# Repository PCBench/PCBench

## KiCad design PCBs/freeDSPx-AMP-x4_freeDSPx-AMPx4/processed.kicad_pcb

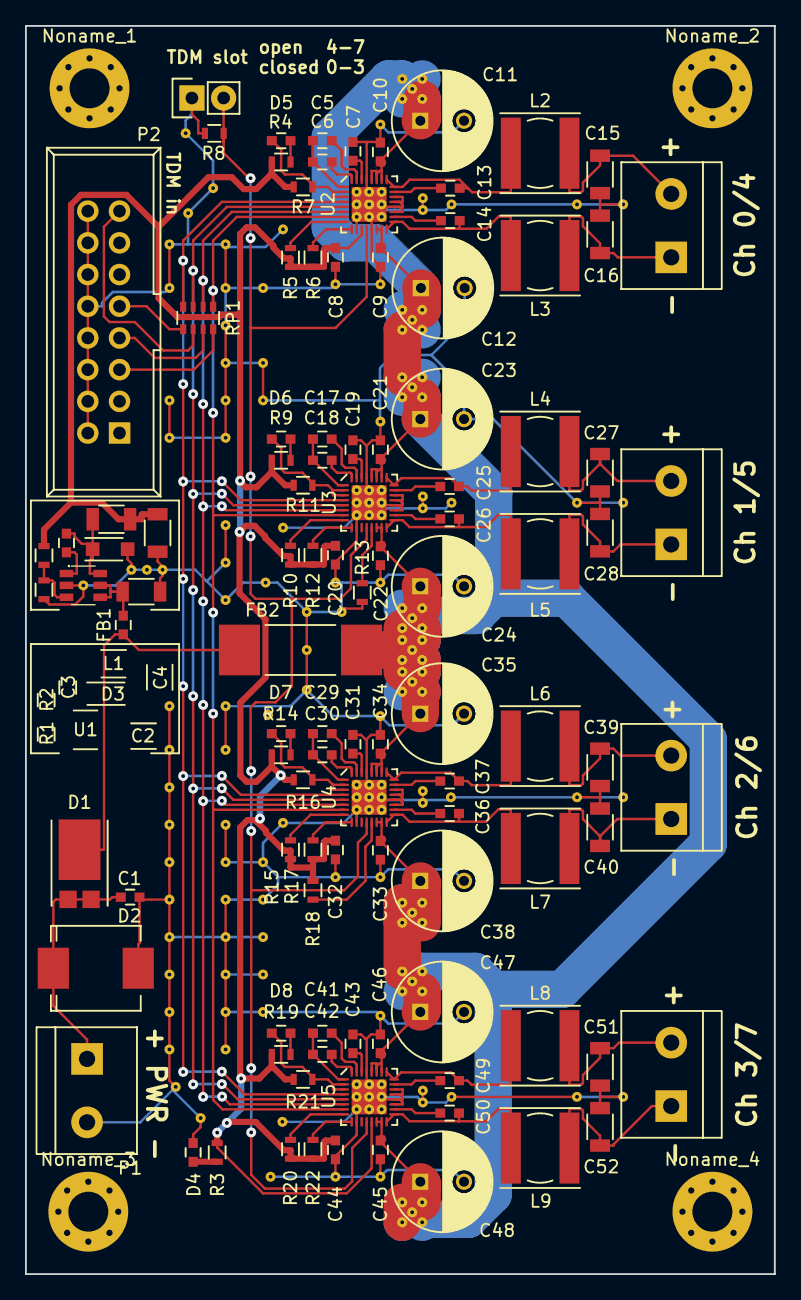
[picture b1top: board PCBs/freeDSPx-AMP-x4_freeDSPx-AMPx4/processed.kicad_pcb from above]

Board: 2 copper layers, 60.0 x 100.0 mm, 283 parts (0 on the bottom side), 77 nets.

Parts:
C1, C3, C9, C10, C21, C22, C33, C34, C45, C46: 100n/50V; C_0603
C2: 10u/35V; C_1206
C4: 22u/10V; C_1206
C5, C6, C7, C8, C17, C18, C19, C20, C29, C30, C31, C32, C41, C42, C43, C44: 1u/16V; C_0603
C11, C12, C23, C24, C35, C36, C47, C48: 100u/35V; C_Radial_D8_L11.5_P3.5
C13, C14, C25, C26, C37, C38, C49, C50: 220n/25V; C_0603
C15, C16, C27, C28, C39, C40, C51, C52: 680n/50V; C_1206
D1: SBR10E45P5; PowerDI5
D2: 5.0SMDJ28CA; SMC
D3: PMEG6010ER; SOD-123W
D4, D5, D6, D7, D8: LED; C_0603
FB1: 470; C_0603
FB2: 115; C_3312
JP1: JUMPER; Pin_Header_Straight_1x02
L1: 47u; L_1207
L2, L3, L4, L5, L6, L7, L8, L9: 15u; Choke_SMD_6.0x6.0
Noname_1, Noname_2, Noname_3, Noname_4: MountingHole_3.2mm_M3_Pad_Via
None_1, None_2, None_3, None_4, None_5, None_6, None_7, None_8, None_9, None_10, None_11, None_12, None_13, None_14, None_15, None_16, None_17, None_18, None_19, None_20, None_21, None_22, None_23, None_24, None_25, None_26, None_27, None_28, None_29, None_30, None_31, None_32, None_33, None_34, None_35, None_36, None_37, None_38, None_39, None_40, None_41, None_42, None_43, None_44, None_45, None_46, None_47, None_48, None_49, None_50, None_51, None_52, None_53, None_54, None_55, None_56, None_57, None_58, None_59, None_60, None_61, None_62, None_63, None_64, None_65, None_66, None_67, None_68, None_69, None_70, None_71, None_72, None_73, None_74, None_75, None_76, None_77, None_78, None_79, None_80, None_81, None_82, None_83, None_84, None_85, None_86, None_87, None_88, None_89, None_90, None_91, None_92, None_93, None_94, None_95, None_96, None_97, None_98, None_99, None_100, None_101, None_102, None_103, None_104, None_105, None_106, None_107, None_108, None_109, None_110, None_111, None_112, None_113, None_114, None_115, None_116, None_117, None_118, None_119, None_120, None_121, None_122, None_123, None_124, None_125, None_126, None_127, None_128, None_129, None_130, None_131, None_132, None_133, None_134, None_135, None_136, None_137, None_138, None_139, None_140, None_141, None_142, None_143, None_144, None_145, None_146, None_147, None_148, None_149, None_150, None_151, None_152, None_153, None_154, None_155, None_156, None_157, None_158, None_159, None_160, None_161, None_162, None_163, None_164, None_165, None_166, None_167, None_168, None_169, None_170, None_171, None_172, None_173: Via_0.3mm_0.8mm
P1, P3, P4, P5, P6: CONN_01X02; RIACON101-2
P2: STDCONN; IDC_Header_Straight_16pins
R1: 1k2; R_0603
R2: 3k4; R_0603
R3, R4, R9, R14, R19: 620; R_0603
R5, R6, R10, R12, R15, R17, R20, R22: 2k4; R_0603
R7, R11, R16, R21: 100k; R_0603
R8, R13, R18: 22k; R_0603
RP1: 33; R_Array_Convex_4x0603
U1: LM2841X; SOT23-6_1.7x3.0mm_Pitch0.95mm
U2, U3, U4, U5: TAS5720M; VQFN-32_4x4mm_Pitch0.4mm

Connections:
+3V3: C4.2, C8.2, C20.2, C32.2, C44.2, L1.2, R2.1, R3.2, R4.1, R5.1, R6.1, R7.1, R9.1, R10.1, R11.1, R12.1, R14.1, R15.1, R16.1, R17.1, R18.2, R19.1, R20.1, R21.1, R22.1, U2.11, U5.13
ADRESS: JP1.2, R8.2, U2.12, U3.12, U4.12, U5.12
BCLK: RP1.2, U2.6, U3.6, U4.6, U5.6
GND: C1.1, C2.1, C4.1, C7.1, C8.1, C9.2, C10.2, C11.2, C12.2, C15.1, C16.1, C19.1, C20.1, C21.2, C22.2, C23.2, C24.2, C27.1, C28.1, C31.1, C32.1, C33.2, C34.2, C35.2, C36.2, C39.1, C40.1, C43.1, C44.1, C45.2, C46.2, C47.2, C48.2, C51.1, C52.1, D2.2, D3.2, D4.1, JP1.1, None_1.1, None_2.1, None_3.1, None_4.1, None_5.1, None_6.1, None_7.1, None_8.1, None_9.1, None_10.1, None_11.1, None_12.1, None_13.1, None_14.1, None_15.1, None_21.1, None_22.1, None_28.1, None_29.1, None_30.1, None_31.1, None_37.1, None_38.1, None_39.1, None_40.1, None_41.1, None_43.1, None_44.1, None_46.1, None_50.1, None_51.1, None_52.1, None_53.1, None_54.1, None_56.1, None_57.1, None_67.1, None_68.1, None_69.1, None_70.1, None_71.1, None_72.1, None_73.1, None_74.1, None_75.1, None_76.1, None_77.1, None_78.1, None_79.1, None_85.1, None_86.1, None_87.1, None_88.1, None_89.1, None_90.1, None_91.1, None_92.1, None_93.1, None_94.1, None_95.1, None_101.1, None_102.1, None_103.1, None_104.1, None_110.1, None_111.1, None_112.1, None_113.1, None_114.1, None_115.1, None_116.1, None_117.1, None_118.1, None_119.1, None_120.1, None_121.1, None_122.1, None_123.1, None_124.1, None_125.1, None_126.1, None_127.1, None_128.1, None_129.1, None_130.1, None_131.1, None_132.1, None_133.1, None_134.1, None_135.1, None_136.1, None_137.1, None_138.1, None_139.1, None_140.1, None_141.1, None_142.1, None_143.1, None_144.1, None_145.1, None_146.1, None_147.1, None_148.1, None_149.1, None_150.1, None_151.1, None_152.1, None_153.1, None_154.1, None_155.1, None_156.1, None_157.1, None_158.1, None_159.1, None_160.1, None_161.1, None_162.1, None_163.1, None_164.1, None_165.1, None_166.1, None_167.1, None_168.1, None_169.1, None_170.1, None_171.1, None_172.1, None_173.1, P1.2, P2.2, P2.4, P2.6, P2.8, P2.10, P2.12, P2.14, P2.16, R1.1, R8.1, R13.1, U1.2, U2.10, U2.13, U2.19, U2.20, U2.21, U2.22, U2.29, U2.33, U3.10, U3.19, U3.20, U3.21, U3.22, U3.29, U3.33, U4.10, U4.19, U4.20, U4.21, U4.22, U4.29, U4.33, U5.10, U5.19, U5.20, U5.21, U5.22, U5.29, U5.33
LRCLK: RP1.4, U2.4, U3.4, U4.4, U5.4
MCLK: RP1.3, U2.5, U3.5, U4.5, U5.5
unnamed: C1.2, D1.2, D2.1, P1.1
unnamed: C2.2, FB1.2, U1.4, U1.5
unnamed: C3.1, U1.1
unnamed: C3.2, D3.1, L1.1, U1.6
unnamed: C5.1, U2.31
unnamed: C5.2, C6.2, U2.1
unnamed: C6.1, U2.32
unnamed: C7.2, U2.30
unnamed: C13.1, U2.23
unnamed: C13.2, L2.1, U2.24, U2.25
unnamed: C14.1, L3.1, U2.16, U2.17
unnamed: C14.2, U2.18
unnamed: C15.2, L2.2, P3.2
unnamed: C16.2, L3.2, P3.1
unnamed: C17.1, U3.31
unnamed: C17.2, C18.2, U3.1
unnamed: C18.1, U3.32
unnamed: C19.2, U3.30
unnamed: C25.1, U3.23
unnamed: C25.2, L4.1, U3.24, U3.25
unnamed: C26.1, L5.1, U3.16, U3.17
unnamed: C26.2, U3.18
unnamed: C27.2, L4.2, P4.2
unnamed: C28.2, L5.2, P4.1
unnamed: C29.1, U4.31
unnamed: C29.2, C30.2, U4.1
unnamed: C30.1, U4.32
unnamed: C31.2, U4.30
unnamed: C37.1, U4.23
unnamed: C37.2, L6.1, U4.24, U4.25
unnamed: C38.1, L7.1, U4.16, U4.17
unnamed: C38.2, U4.18
unnamed: C39.2, L6.2, P5.2
unnamed: C40.2, L7.2, P5.1
unnamed: C41.1, U5.31
unnamed: C41.2, C42.2, U5.1
unnamed: C42.1, U5.32
unnamed: C43.2, U5.30
unnamed: C49.1, U5.23
unnamed: C49.2, L8.1, U5.24, U5.25
unnamed: C50.1, L9.1, U5.16, U5.17
unnamed: C50.2, U5.18
unnamed: C51.2, L8.2, P6.2
unnamed: C52.2, L9.2, P6.1
unnamed: D4.2, R3.1
unnamed: D5.1, R7.2, U2.2, U2.3
unnamed: D5.2, R4.2
unnamed: D6.1, R11.2, U3.2, U3.3
unnamed: D6.2, R9.2
unnamed: D7.1, R16.2, U4.2, U4.3
unnamed: D7.2, R14.2
unnamed: D8.1, R21.2, U5.2, U5.3
unnamed: D8.2, R19.2
unnamed: P2.5, RP1.8
unnamed: P2.7, RP1.7
unnamed: P2.9, RP1.5
unnamed: P2.15, RP1.6
unnamed: R1.2, R2.2, U1.3
unnamed: R5.2, U2.8
unnamed: R6.2, U2.9
unnamed: R10.2, U3.8
unnamed: R12.2, U3.9
unnamed: R13.2, U3.13
unnamed: R15.2, U4.8
unnamed: R17.2, U4.9
unnamed: R18.1, U4.13
unnamed: R20.2, U5.8
unnamed: R22.2, U5.9
SDATA: RP1.1, U2.7, U3.7, U4.7, U5.7
VCC: C9.1, C10.1, C11.1, C12.1, C21.1, C22.1, C23.1, C24.1, C33.1, C34.1, C35.1, C36.1, C45.1, C46.1, C47.1, C48.1, FB2.2, None_16.1, None_17.1, None_18.1, None_19.1, None_20.1, None_23.1, None_24.1, None_25.1, None_26.1, None_27.1, None_32.1, None_33.1, None_34.1, None_35.1, None_36.1, None_42.1, None_45.1, None_47.1, None_48.1, None_49.1, None_55.1, None_58.1, None_59.1, None_60.1, None_61.1, None_62.1, None_63.1, None_64.1, None_65.1, None_66.1, None_80.1, None_81.1, None_82.1, None_83.1, None_84.1, None_96.1, None_97.1, None_98.1, None_99.1, None_100.1, None_105.1, None_106.1, None_107.1, None_108.1, None_109.1, U2.14, U2.15, U2.26, U2.27, U2.28, U3.14, U3.15, U3.26, U3.27, U3.28, U4.14, U4.15, U4.26, U4.27, U4.28, U5.14, U5.15, U5.26, U5.27, U5.28
VIN: D1.1, FB1.1, FB2.1

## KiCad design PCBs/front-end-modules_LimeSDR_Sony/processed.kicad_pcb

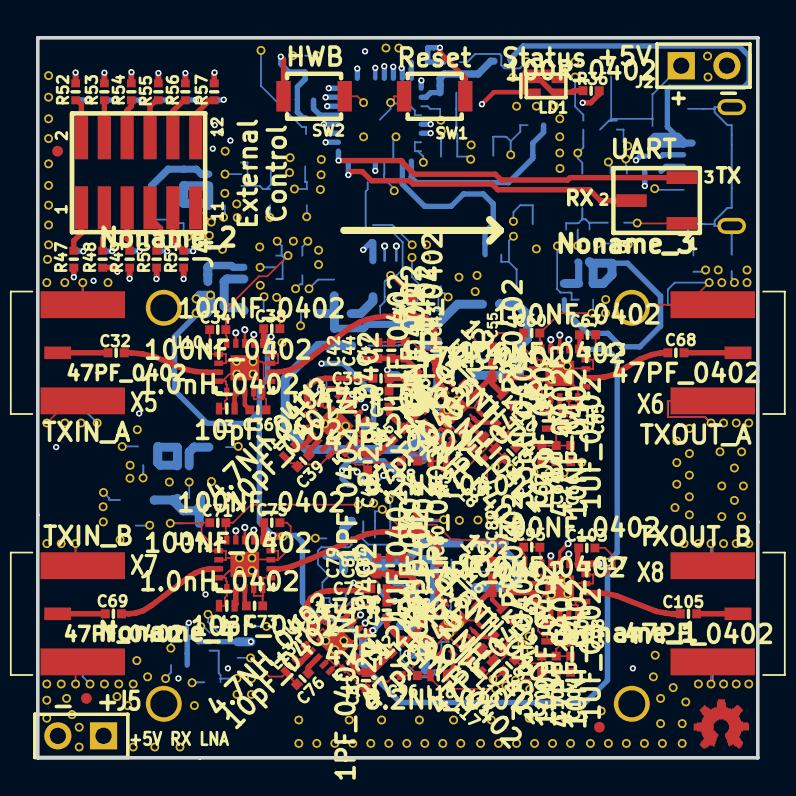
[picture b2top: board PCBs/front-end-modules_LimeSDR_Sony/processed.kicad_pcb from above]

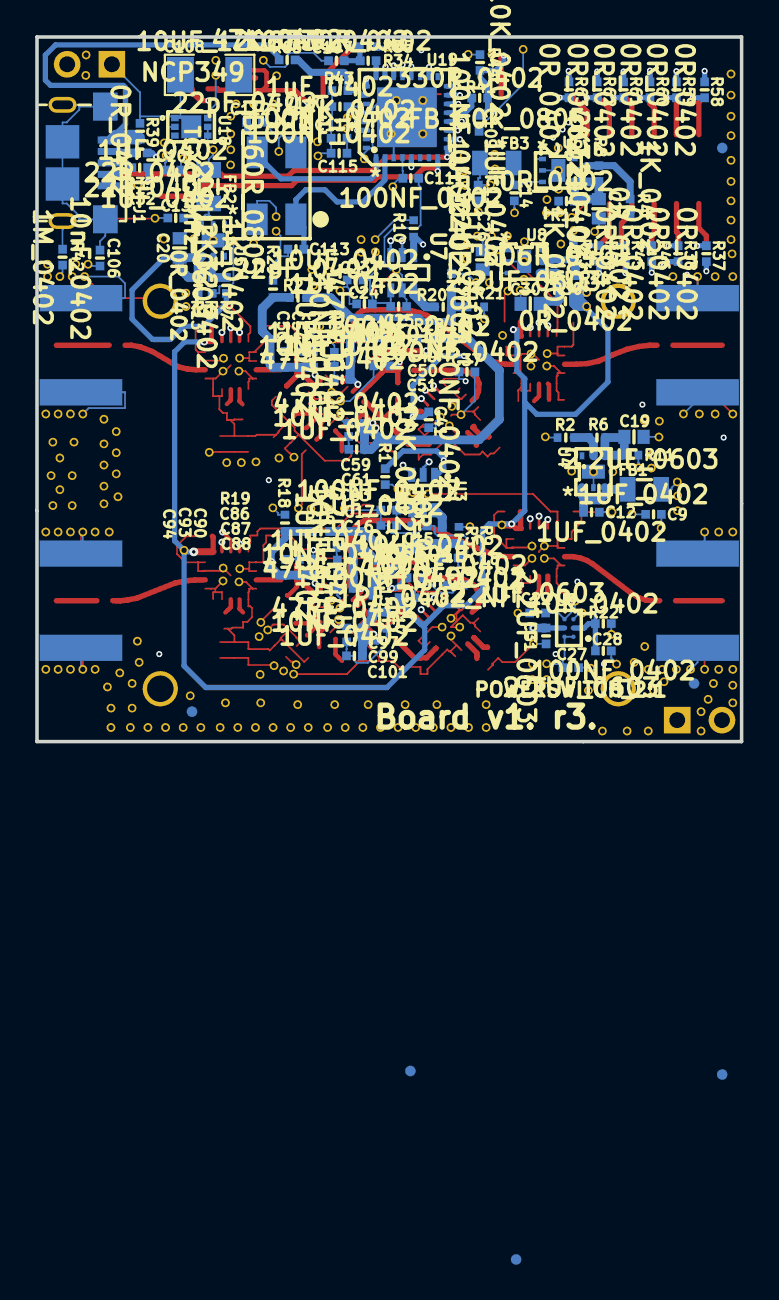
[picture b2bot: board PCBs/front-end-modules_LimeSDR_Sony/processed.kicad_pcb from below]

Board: 6 copper layers, 40.0 x 40.0 mm, 529 parts (129 on the bottom side), 124 nets.

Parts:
ASTUB: VAL**; ASTUB
C9, C10, C11, C12, C13, C14, C16, C18, C24, C29, C42, C49, C56, C63, C66, C79, C86, C94, C101, C104: 1UF_0402; SMD0402
C15, C23: 10UF_0402; SMD0402
C17, C25, C28, C34, C37, C38, C41, C60, C67, C71, C74, C75, C78, C95, C103, C107, C109, C111, C114, C115: 100NF_0402; SMD0402
C19, C20, C21, C26, C30: 2.2UF_0603; SMD0603
C22, C27, C31: 2.2UF_0603; SMD0402
C32, C69: 47PF_0402; SM0402
C33, C46, C70, C83: 1PF_0402_NF; SMD0402
C35, C47, C51, C52, C53, C57, C58, C59, C62, C68, C72, C84, C88, C90, C91, C92, C96, C97, C100, C105: 47PF_0402; SMD0402
C36, C39, C43, C73, C76, C80: 10pF_0402; SMD0402
C40, C55, C77, C89: 1PF_0402; SMD0402
C44, C50, C54, C61, C64, C81, C87, C93, C99, C102: 10NF_0402; SMD0402
C45, C82: 47pF_0402; SMD0402
C48, C85: 2.2pF_0402; SMD0402
C65, C98: 100pF_0402; SMD0402
C106: 10nF_0402; SMD0402
C108: 10UF_1206; SMD1206
C110: 1uF_0402; SMD0402
C112, C113: 22pF_0402; SMD0402
FB1: FB_60R_0805; SM0805
FB2, FB3: FB_60R_0805; SMD0805
FD1, FD2, FD3, FD4, FD4_2, FD5, FD5_2, FD6, FD6_2: FIDUCIAL; Fiducial
GND_VIA: VAL**; GND_VIA
GND_VIA_2, GND_VIA_3, GND_VIA_4, GND_VIA_5, GND_VIA_6, GND_VIA_7, GND_VIA_8, GND_VIA_9, GND_VIA_10, GND_VIA_11, GND_VIA_12, GND_VIA_13, GND_VIA_14, GND_VIA_15, GND_VIA_16, GND_VIA_17, GND_VIA_18, GND_VIA_19, GND_VIA_20, GND_VIA_21, GND_VIA_22, GND_VIA_23, GND_VIA_24, GND_VIA_25, GND_VIA_26, GND_VIA_27, GND_VIA_28, GND_VIA_29, GND_VIA_30, GND_VIA_31, GND_VIA_32, GND_VIA_33, GND_VIA_34, GND_VIA_35, GND_VIA_36, GND_VIA_37, GND_VIA_38, GND_VIA_39, GND_VIA_40, GND_VIA_41, GND_VIA_42, GND_VIA_43, GND_VIA_44, GND_VIA_45, GND_VIA_46, GND_VIA_47, GND_VIA_48, GND_VIA_49, GND_VIA_50, GND_VIA_51, GND_VIA_52, GND_VIA_53, GND_VIA_54, GND_VIA_55, GND_VIA_56, GND_VIA_57, GND_VIA_58, GND_VIA_59, GND_VIA_60, GND_VIA_61, GND_VIA_62, GND_VIA_63, GND_VIA_64, GND_VIA_65, GND_VIA_66, GND_VIA_67, GND_VIA_68, GND_VIA_69, GND_VIA_70, GND_VIA_71, GND_VIA_72, GND_VIA_73, GND_VIA_74, GND_VIA_75, GND_VIA_76, GND_VIA_77, GND_VIA_78, GND_VIA_79, GND_VIA_80, GND_VIA_81, GND_VIA_82, GND_VIA_83, GND_VIA_84, GND_VIA_85, GND_VIA_86, GND_VIA_87, GND_VIA_88, GND_VIA_89, GND_VIA_90, GND_VIA_91, GND_VIA_92, GND_VIA_93, GND_VIA_94, GND_VIA_95, GND_VIA_96, GND_VIA_97, GND_VIA_98, GND_VIA_99, GND_VIA_100, GND_VIA_101, GND_VIA_102, GND_VIA_103, GND_VIA_104, GND_VIA_105, GND_VIA_106, GND_VIA_107, GND_VIA_108, GND_VIA_109, GND_VIA_110, GND_VIA_111, GND_VIA_112, GND_VIA_113, GND_VIA_114, GND_VIA_115, GND_VIA_116, GND_VIA_117, GND_VIA_118, GND_VIA_119, GND_VIA_120, GND_VIA_121, GND_VIA_122, GND_VIA_123, GND_VIA_124, GND_VIA_125, GND_VIA_126, GND_VIA_127, GND_VIA_128, GND_VIA_129, GND_VIA_130, GND_VIA_131, GND_VIA_132, GND_VIA_133, GND_VIA_134, GND_VIA_135, GND_VIA_136, GND_VIA_137, GND_VIA_138, GND_VIA_139, GND_VIA_140, GND_VIA_141, GND_VIA_142, GND_VIA_143, GND_VIA_144, GND_VIA_145, GND_VIA_146, GND_VIA_147, GND_VIA_148, GND_VIA_149, GND_VIA_150, GND_VIA_151, GND_VIA_152, GND_VIA_153, GND_VIA_154, GND_VIA_155, GND_VIA_156, GND_VIA_157, GND_VIA_158, GND_VIA_159, GND_VIA_160, GND_VIA_161, GND_VIA_162, GND_VIA_163, GND_VIA_164, GND_VIA_165, GND_VIA_166, GND_VIA_167, GND_VIA_168, GND_VIA_169, GND_VIA_170, GND_VIA_171, GND_VIA_172, GND_VIA_173, GND_VIA_174, GND_VIA_175, GND_VIA_176, GND_VIA_177, GND_VIA_178, GND_VIA_179, GND_VIA_180, GND_VIA_181, GND_VIA_182, GND_VIA_183, GND_VIA_184, GND_VIA_185, GND_VIA_186, GND_VIA_187, GND_VIA_188, GND_VIA_189, GND_VIA_190, GND_VIA_191, GND_VIA_192, GND_VIA_193, GND_VIA_194, GND_VIA_195, GND_VIA_196, GND_VIA_197, GND_VIA_198, GND_VIA_199, GND_VIA_200, GND_VIA_201, GND_VIA_202, GND_VIA_203, GND_VIA_204, GND_VIA_205, GND_VIA_206, GND_VIA_207, GND_VIA_208, GND_VIA_209, GND_VIA_210, GND_VIA_211, GND_VIA_212, GND_VIA_213, GND_VIA_214, GND_VIA_215, GND_VIA_216, GND_VIA_217, GND_VIA_218, GND_VIA_219, GND_VIA_220, GND_VIA_221, GND_VIA_222, GND_VIA_223, GND_VIA_224, GND_VIA_225, GND_VIA_226, GND_VIA_227, GND_VIA_228, GND_VIA_229, GND_VIA_230, GND_VIA_231, GND_VIA_232, GND_VIA_233, GND_VIA_234, GND_VIA_235, GND_VIA_236, GND_VIA_237, GND_VIA_238, GND_VIA_239, GND_VIA_240, GND_VIA_241, GND_VIA_242, GND_VIA_243, GND_VIA_244, GND_VIA_245, GND_VIA_246, GND_VIA_247, GND_VIA_248, GND_VIA_249, GND_VIA_250, GND_VIA_251, GND_VIA_252, GND_VIA_253, GND_VIA_254, GND_VIA_255, GND_VIA_256, GND_VIA_257, GND_VIA_258, GND_VIA_259, GND_VIA_260, GND_VIA_261, GND_VIA_262, GND_VIA_263, GND_VIA_264, GND_VIA_265, GND_VIA_266, GND_VIA_267, GND_VIA_268, GND_VIA_269, GND_VIA_270, GND_VIA_271, GND_VIA_272, GND_VIA_273, GND_VIA_274, GND_VIA_275, GND_VIA_276, GND_VIA_277, GND_VIA_278, GND_VIA_279, GND_VIA_280, GND_VIA_281, GND_VIA_282, GND_VIA_283, GND_VIA_284, GND_VIA_285, GND_VIA_286, GND_VIA_287, GND_VIA_288, GND_VIA_289, GND_VIA_290, GND_VIA_291, GND_VIA_292: VAL**; GND_VIA
J1: MICRO_USB2_B; microUSB2
J2: pinhead_2_NF; pinhead2
J3: PINHEADER_1X3_SM; Pinhead_1x3_SMD
J4: Pinheader_2x6_SMD_1.27; Pinhead_2x6_SMD
J5: pinhead_2; pinhead2
L3, L12: 1.0nH_0402; IND_0402
L4, L13: 4.7NH_0402; IND_0402
L5, L6, L10, L14, L15, L19: 12NH_0402; IND_0402
L7, L16: 22NH_0402; IND_0402
L8, L17: 5.6NH_0402; IND_0402
L9, L18: 8.2NH_0402; IND_0402
L11, L20: 3.3nH_0402; IND_0402
LD1: LED_0603_GR
Noname_1, Noname_2, Noname_3, Noname_4: mounting_via_2
R1, R22, R44: 10K_0402; SMD0402
R2, R6: 200R_0402; R_SM0402
R3, R4, R23: 1K_0402; SMD0402
R5, R13: 0R_0402; SM0402
R7, R8: 2K32_0402; SMD0402
R9, R21: 0R_0402_NF; R_SM0402
R10: 10K_0402; R_SM0402
R11, R20, R47, R48, R49, R50, R51, R52, R53, R54, R55, R56, R57: 0R_0402; R_SM0402
R12, R30, R37, R38, R39, R45, R46, R58, R59, R60, R61, R62, R63, R64: 0R_0402; SMD0402
R14, R15, R16, R25, R26, R27: 15K_0402; R_SM0402
R17, R18, R19, R28, R29, R31: 4K3_0402; R_SM0402
R24: 806R_0402; SMD0402
R32, R33: 22R_0402; SMD0402
R34, R41: 330R_0402; SMD0402
R35: 33K_0402; R_SM0402
R36: 100R_0402; SMD0402
R42: 1M_0402; SMD0402
R43, R65: 47K_0402; SMD0402
SW1, SW2: SW_Tactile; SW_B3U-1000P
U3, U7: AD5601B; SC-70-6
U4, U5, U6, U8: MIC37122YMT_ADJ_6TMLF; 6TMLF
U9: POWERSWITCH_2:1; 6-UFBGA
U10, U11, U13, U14, U15, U17: CXM3624UR; UQFN_18
U12, U16: CXGXXXX; 20PIN-VQFN
U18: NCP349; 6-DFN
U19: AT90USB162-16MUR; VQFN32
X5, X7: SMA_PLUG; SMA
X6, X8: SMA_edge; SMA
XT1: TCXO_8MHz; XO_4DFN
open harware: VAL**; OS_Logo

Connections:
+1.8V: C38.2, C41.2, C67.2, C75.2, C78.2, C103.2, GND_VIA_122.1, GND_VIA_123.1, GND_VIA_124.1, GND_VIA_125.1, GND_VIA_126.1, GND_VIA_127.1, R30.2, U10.14, U11.14, U13.14, U14.14, U15.14, U17.14
+2V: C22.1, GND_VIA_159.1, GND_VIA_160.1, GND_VIA_161.1, GND_VIA_162.1, GND_VIA_164.1, GND_VIA_165.1, R9.1, R11.2, R21.1, U9.C2
+3.3V: C15.1, C16.1, C17.1, C23.1, C24.1, C25.1, C26.1, C34.2, C37.2, C60.2, C71.2, C74.2, C95.2, GND_VIA_43.1, GND_VIA_44.1, GND_VIA_45.1, GND_VIA_46.1, GND_VIA_61.1, GND_VIA_62.1, GND_VIA_63.1, GND_VIA_64.1, GND_VIA_75.1, GND_VIA_97.1, GND_VIA_98.1, GND_VIA_99.1, GND_VIA_100.1, GND_VIA_101.1, GND_VIA_102.1, GND_VIA_134.1, GND_VIA_135.1, R1.1, R10.1, R13.2, U3.4, U7.4, U8.1, U8.3, U10.18, U11.18, U13.18, U14.18, U15.18, U17.18
+3.3V_uC: C110.1, C111.1, C114.1, C115.1, GND_VIA_103.1, GND_VIA_104.1, GND_VIA_105.1, GND_VIA_106.1, GND_VIA_107.1, GND_VIA_108.1, GND_VIA_109.1, GND_VIA_110.1, GND_VIA_111.1, GND_VIA_112.1, GND_VIA_113.1, R12.2, R35.2, R44.2, U19.4, U19.27, U19.31, U19.32
+5V: C9.1, C10.1, C11.1, C27.1, C53.2, C58.1, C62.1, C64.1, C66.1, C91.2, C96.1, C100.1, C102.1, C104.1, FB1.1, FB2.1, FB3.1, GND_VIA.1, GND_VIA_2.1, GND_VIA_29.1, GND_VIA_30.1, GND_VIA_31.1, GND_VIA_32.1, GND_VIA_33.1, GND_VIA_34.1, GND_VIA_35.1, GND_VIA_47.1, GND_VIA_48.1, GND_VIA_49.1, GND_VIA_50.1, GND_VIA_51.1, GND_VIA_52.1, GND_VIA_53.1, GND_VIA_54.1, GND_VIA_55.1, GND_VIA_56.1, GND_VIA_57.1, GND_VIA_58.1, GND_VIA_59.1, GND_VIA_60.1, GND_VIA_74.1, GND_VIA_76.1, GND_VIA_77.1, GND_VIA_78.1, GND_VIA_79.1, GND_VIA_114.1, GND_VIA_115.1, GND_VIA_116.1, GND_VIA_117.1, GND_VIA_118.1, GND_VIA_119.1, GND_VIA_120.1, GND_VIA_121.1, GND_VIA_128.1, GND_VIA_129.1, J5.1, L8.1, L9.1, L10.1, L17.1, L18.1, L19.1, U9.A1, U9.A2, U18.4, U18.5
/Microcontroller/DATA+: J1.3, R32.1
/Microcontroller/DATA-: J1.2, R33.1
/Microcontroller/LED_G: R36.1, U19.21
/Microcontroller/LED_R: LD1.2, LD1.3, U19.20
/Microcontroller/UART_RX: J3.2, U19.8
/Microcontroller/UART_TX: J3.3, U19.9
/Microcontroller/VBUS: J1.1, R39.2, R65.2
GND: C9.2, C10.2, C11.2, C12.2, C13.2, C14.2, C15.2, C16.2, C17.2, C18.2, C19.2, C20.2, C21.2, C22.2, C23.2, C24.2, C25.2, C26.2, C27.2, C28.2, C29.2, C30.2, C31.2, C33.2, C34.1, C36.2, C37.1, C38.1, C39.2, C40.2, C41.1, C42.2, C44.2, C46.2, C47.2, C49.2, C50.2, C51.2, C52.2, C53.1, C54.2, C55.2, C56.2, C58.2, C59.2, C60.1, C61.2, C62.2, C63.2, C64.2, C65.2, C66.2, C67.1, C70.2, C71.1, C73.2, C74.1, C75.1, C76.2, C77.2, C78.1, C79.2, C81.2, C83.2, C84.2, C86.2, C87.2, C88.2, C89.2, C90.2, C91.1, C93.2, C94.2, C95.1, C96.2, C97.2, C98.2, C99.2, C100.2, C101.2, C102.2, C103.1, C104.2, C106.2, C107.2, C108.2, C109.2, C110.2, C111.2, C112.1, C113.1, C114.2, C115.2, GND_VIA_3.1, GND_VIA_4.1, GND_VIA_5.1, GND_VIA_6.1, GND_VIA_7.1, GND_VIA_8.1, GND_VIA_9.1, GND_VIA_10.1, GND_VIA_11.1, GND_VIA_12.1, GND_VIA_13.1, GND_VIA_14.1, GND_VIA_15.1, GND_VIA_16.1, GND_VIA_17.1, GND_VIA_18.1, GND_VIA_19.1, GND_VIA_20.1, GND_VIA_21.1, GND_VIA_22.1, GND_VIA_23.1, GND_VIA_24.1, GND_VIA_25.1, GND_VIA_26.1, GND_VIA_27.1, GND_VIA_28.1, GND_VIA_36.1, GND_VIA_37.1, GND_VIA_38.1, GND_VIA_39.1, GND_VIA_40.1, GND_VIA_41.1, GND_VIA_42.1, GND_VIA_65.1, GND_VIA_66.1, GND_VIA_67.1, GND_VIA_68.1, GND_VIA_69.1, GND_VIA_70.1, GND_VIA_71.1, GND_VIA_72.1, GND_VIA_73.1, GND_VIA_80.1, GND_VIA_81.1, GND_VIA_82.1, GND_VIA_83.1, GND_VIA_84.1, GND_VIA_85.1, GND_VIA_86.1, GND_VIA_87.1, GND_VIA_88.1, GND_VIA_89.1, GND_VIA_90.1, GND_VIA_91.1, GND_VIA_92.1, GND_VIA_93.1, GND_VIA_94.1, GND_VIA_95.1, GND_VIA_96.1, GND_VIA_130.1, GND_VIA_131.1, GND_VIA_132.1, GND_VIA_133.1, GND_VIA_136.1, GND_VIA_137.1, GND_VIA_138.1, GND_VIA_139.1, GND_VIA_140.1, GND_VIA_141.1, GND_VIA_142.1, GND_VIA_143.1, GND_VIA_144.1, GND_VIA_145.1, GND_VIA_146.1, GND_VIA_147.1, GND_VIA_148.1, GND_VIA_149.1, GND_VIA_150.1, GND_VIA_151.1, GND_VIA_152.1, GND_VIA_153.1, GND_VIA_154.1, GND_VIA_155.1, GND_VIA_156.1, GND_VIA_157.1, GND_VIA_158.1, GND_VIA_163.1, GND_VIA_166.1, GND_VIA_167.1, GND_VIA_168.1, GND_VIA_169.1, GND_VIA_170.1, GND_VIA_171.1, GND_VIA_172.1, GND_VIA_173.1, GND_VIA_174.1, GND_VIA_175.1, GND_VIA_176.1, GND_VIA_177.1, GND_VIA_178.1, GND_VIA_179.1, GND_VIA_180.1, GND_VIA_181.1, GND_VIA_182.1, GND_VIA_183.1, GND_VIA_184.1, GND_VIA_185.1, GND_VIA_186.1, GND_VIA_187.1, GND_VIA_188.1, GND_VIA_189.1, GND_VIA_190.1, GND_VIA_191.1, GND_VIA_192.1, GND_VIA_193.1, GND_VIA_194.1, GND_VIA_195.1, GND_VIA_196.1, GND_VIA_197.1, GND_VIA_198.1, GND_VIA_199.1, GND_VIA_200.1, GND_VIA_201.1, GND_VIA_202.1, GND_VIA_203.1, GND_VIA_204.1, GND_VIA_205.1, GND_VIA_206.1, GND_VIA_207.1, GND_VIA_208.1, GND_VIA_209.1, GND_VIA_210.1, GND_VIA_211.1, GND_VIA_212.1, GND_VIA_213.1, GND_VIA_214.1, GND_VIA_215.1, GND_VIA_216.1, GND_VIA_217.1, GND_VIA_218.1, GND_VIA_219.1, GND_VIA_220.1, GND_VIA_221.1, GND_VIA_222.1, GND_VIA_223.1, GND_VIA_224.1, GND_VIA_225.1, GND_VIA_226.1, GND_VIA_227.1, GND_VIA_228.1, GND_VIA_229.1, GND_VIA_230.1, GND_VIA_231.1, GND_VIA_232.1, GND_VIA_233.1, GND_VIA_234.1, GND_VIA_235.1, GND_VIA_236.1, GND_VIA_237.1, GND_VIA_238.1, GND_VIA_239.1, GND_VIA_240.1, GND_VIA_241.1, GND_VIA_242.1, GND_VIA_243.1, GND_VIA_244.1, GND_VIA_245.1, GND_VIA_246.1, GND_VIA_247.1, GND_VIA_248.1, GND_VIA_249.1, GND_VIA_250.1, GND_VIA_251.1, GND_VIA_252.1, GND_VIA_253.1, GND_VIA_254.1, GND_VIA_255.1, GND_VIA_256.1, GND_VIA_257.1, GND_VIA_258.1, GND_VIA_259.1, GND_VIA_260.1, GND_VIA_261.1, GND_VIA_262.1, GND_VIA_263.1, GND_VIA_264.1, GND_VIA_265.1, GND_VIA_266.1, GND_VIA_267.1, GND_VIA_268.1, GND_VIA_269.1, GND_VIA_270.1, GND_VIA_271.1, GND_VIA_272.1, GND_VIA_273.1, GND_VIA_274.1, GND_VIA_275.1, GND_VIA_276.1, GND_VIA_277.1, GND_VIA_278.1, GND_VIA_279.1, GND_VIA_280.1, GND_VIA_281.1, GND_VIA_282.1, GND_VIA_283.1, GND_VIA_284.1, GND_VIA_285.1, GND_VIA_286.1, GND_VIA_287.1, GND_VIA_288.1, GND_VIA_289.1, GND_VIA_290.1, GND_VIA_291.1, GND_VIA_292.1, J1.5, J2.2, J3.1, J4.11, J5.2, L3.2, L4.2, L6.2, L7.2, L11.2, L12.2, L13.2, L15.2, L16.2, L20.2, Noname_1.1, Noname_2.1, Noname_3.1, Noname_4.1, R2.1, R3.1, R4.1, R17.2, R18.2, R19.2, R22.1, R23.1, R28.2, R29.2, R31.2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
MCU_SPI_DACA_SS: R10.2, R46.2, R49.2, U7.1
MCU_SPI_DACB_SS: R1.2, R45.2, R50.2, U3.1
MCU_SPI_MOSI: R37.2, R47.2, U3.3, U7.3, U10.15, U11.15, U13.15, U14.15, U15.15, U17.15
MCU_SPI_SCLK: R38.2, R48.2, U3.2, U7.2, U10.16, U11.16, U13.16, U14.16, U15.16, U17.16
MCU_TunerA_IN_SS: R54.1, R60.1, U10.17
MCU_TunerA_MID_SS: R53.1, R59.1, U11.17
MCU_TunerA_OUT_SS: R52.1, R58.1, U13.17
MCU_TunerB_IN_SS: R57.1, R63.1, U14.17
MCU_TunerB_MID_SS: R56.1, R62.1, U15.17
MCU_TunerB_OUT_SS: R55.1, R61.1, U17.17
unnamed: C12.1, FB1.2, U4.1, U4.3
unnamed: C13.1, FB2.2, U5.1, U5.3
unnamed: C14.1, FB3.2, U6.1, U6.3
unnamed: C18.1, R5.2, R9.2, R14.1, R15.1, R16.1
unnamed: C19.1, R6.1, R11.1, U4.4
unnamed: C20.1, R7.2, R13.1, U5.4
unnamed: C21.1, R8.2, R12.1, U6.4
unnamed: C29.1, R20.2, R21.2, R25.1, R26.1, R27.1
unnamed: C30.1, R24.2, R30.1, U8.4
unnamed: C32.1, X5.1
unnamed: C32.2, U10.3
unnamed: C33.1, C35.2, C48.1, L5.1, U12.15
unnamed: C35.1, U11.3
unnamed: C36.1, U10.7
unnamed: C39.1, U11.7
unnamed: C40.1, C43.1, U10.11
unnamed: C43.2, U12.12
unnamed: C45.1, C46.1, U11.11
unnamed: C45.2, C48.2, U12.16
unnamed: C55.1, C57.2, L10.2, U12.8
unnamed: C57.1, U13.3
unnamed: C65.1, U13.7
unnamed: C68.1, U13.11
unnamed: C68.2, X6.1
unnamed: C69.1, X7.1
unnamed: C69.2, U14.3
unnamed: C70.1, C72.2, C85.1, L14.1, U16.15
unnamed: C72.1, U15.3
unnamed: C73.1, U14.7
unnamed: C76.1, U15.7
unnamed: C77.1, C80.1, U14.11
unnamed: C80.2, U16.12
unnamed: C82.1, C83.1, U15.11
unnamed: C82.2, C85.2, U16.16
unnamed: C89.1, C92.2, L19.2, U16.8
unnamed: C92.1, U17.3
unnamed: C98.1, U17.7
unnamed: C105.1, U17.11
unnamed: C105.2, X8.1
unnamed: C106.1, J1.6, R42.1
unnamed: C107.1, R34.2, R35.1, SW1.2
unnamed: C109.1, R41.1, R44.1, SW2.1
unnamed: C112.2, U19.1, XT1.3
unnamed: C113.2, U19.2, XT1.1
unnamed: J4.1, R47.1
unnamed: J4.2, R52.2
unnamed: J4.3, R48.1
unnamed: J4.4, R53.2
unnamed: J4.5, R49.1
unnamed: J4.6, R54.2
unnamed: J4.7, R50.1
unnamed: J4.8, R55.2
unnamed: J4.9, R51.1
unnamed: J4.10, R56.2
unnamed: J4.12, R57.2
unnamed: L3.1, U10.6
unnamed: L4.1, U11.6
unnamed: L6.1, U12.3
unnamed: L7.1, U12.5
unnamed: L8.2, U12.4
unnamed: L9.2, U12.1
unnamed: L11.1, U13.6
unnamed: L12.1, U14.6
unnamed: L13.1, U15.6
unnamed: L15.1, U16.3
unnamed: L16.1, U16.5
unnamed: L17.2, U16.4
unnamed: L18.2, U16.1
unnamed: L20.1, U17.6
unnamed: LD1.1, LD1.4, R36.2
unnamed: R2.2, R6.2, U4.5
unnamed: R3.2, R7.1, U5.5
unnamed: R4.2, R8.1, U6.5
unnamed: R5.1, U3.6
unnamed: R20.1, U7.6
unnamed: R23.2, R24.1, U8.5
unnamed: R32.2, U19.29
unnamed: R33.2, U19.30
unnamed: R34.1, U19.24
unnamed: R37.1, U19.16
unnamed: R38.1, U19.15
unnamed: R41.2, U19.13
unnamed: R43.2, R65.1, U19.26
unnamed: R45.1, U19.18
unnamed: R46.1, U19.14
unnamed: R58.2, U19.25
unnamed: R59.2, U19.23
unnamed: R60.2, U19.22
unnamed: R61.2, U19.12
unnamed: R62.2, U19.11
unnamed: R63.2, U19.10
unnamed: R64.2, U19.5
PWR: C108.1, J2.1, R39.1, U18.1
Vd_Drive_select: C28.1, R22.2, R51.2, R64.1, U9.B1
Vd_Driver: C31.1, C42.1, C44.1, C47.1, C79.1, C81.1, C84.1, L5.2, L14.2, U9.B2
Vg1_2_A: C59.1, C61.1, C63.1, R26.2, R28.1, U12.17, U12.18
Vg1_2_B: C97.1, C99.1, C101.1, R15.2, R17.1, U16.17, U16.18
Vg3_A: C52.1, C54.1, C56.1, R27.2, R29.1, U12.9
Vg3_B: C90.1, C93.1, C94.1, R16.2, R18.1, U16.9
Vg_Driver_A: C49.1, C50.1, C51.1, R25.2, R31.1, U12.14
Vg_Driver_B: C86.1, C87.1, C88.1, R14.2, R19.1, U16.14

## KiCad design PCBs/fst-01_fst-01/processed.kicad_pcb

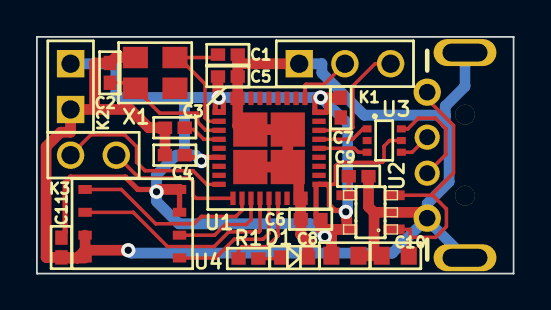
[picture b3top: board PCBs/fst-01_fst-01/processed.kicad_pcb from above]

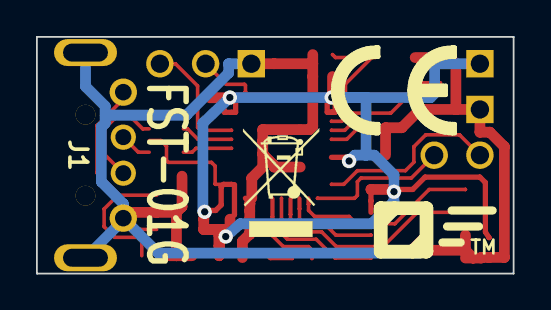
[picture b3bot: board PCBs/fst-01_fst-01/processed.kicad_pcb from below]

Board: 2 copper layers, 26.5 x 13.1 mm, 24 parts (2 on the bottom side), 21 nets.

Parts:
C1, C2: 27pF; c_0402
C3, C4, C5, C6, C7, C11: 0.1uF; c_0402
C8, C10: 4.7uF; c_0603
C9: 0.01uF; c_0402
CE_mark: Symbol_CE_SilkScreen_5mm
D1: LED; LED0603
FST-LOGO: VAL**; FST-LOGO
J1: USB_A; USB-A-PLUG
K1: CONN_3; SIL-3-2
K2: CONN_2; SIL-2-0
K3: CONN_2; SIL-2-2
R1: 510; r_0402
U1: STM32F103TB; QFN36
U2: LP2985-33DBVR; SOT23-5
U3: NUF2221W1; SOT363
U4: SST25VF032B; WSON8
X1: 12MHz; ABM8G

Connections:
+3V3: C4.2, C5.2, C6.2, C7.2, C8.1, C11.2, K2.1, U1.1, U1.6, U1.19, U1.27, U2.5, U3.5, U4.7, U4.8
/CLK: U1.12, U4.6
/D+: U1.24, U3.1
/D+_PLUG: J1.3, U3.6
/D-: U1.23, U3.3
/D-_PLUG: J1.2, U3.4
/LED: R1.2, U1.15
/MISO: U1.13, U4.2
/MOSI: U1.14, U4.5
/NRST: C3.1, U1.4
/NSS: U1.11, U4.1
/OSC_IN: C1.1, U1.2, X1.1
/OSC_OUT: C2.1, U1.3, X1.2
/PA2: K3.1, U1.9
/PA3: K3.2, U1.10
/SWCLK: K1.2, U1.28
/SWDIO: K1.3, U1.25
/VBUS: C10.1, J1.1, U2.1, U2.3
GND: C1.2, C2.2, C3.2, C4.1, C5.1, C6.1, C8.2, C9.2, C10.2, C11.1, D1.1, J1.4, J1.5, K1.1, K2.2, U1.17, U1.18, U1.35, U1.36, U2.2, U4.3, U4.4, X1.3
unnamed: C9.1, U2.4
unnamed: D1.2, R1.1

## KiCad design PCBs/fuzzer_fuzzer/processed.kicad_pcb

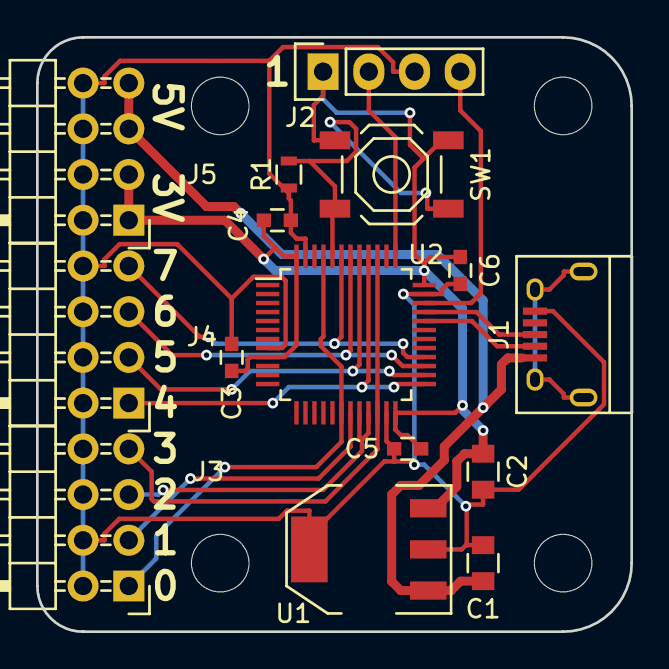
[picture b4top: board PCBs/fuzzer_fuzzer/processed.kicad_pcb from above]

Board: 2 copper layers, 33.0 x 33.0 mm, 15 parts (0 on the bottom side), 16 nets.

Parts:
C1, C2: 1u; C_0805
C3, C4, C5, C6: 100n; C_0603
J1: USB_OTG; USB_Micro-B
J2: CONN_01X04; Pin_Header_Straight_1x04
J3, J4, J5: CONN_02X04; Pin_Header_Angled_2x04
R1: 10K; R_0603
SW1: SPST; SW_SPST_TL3342
U1: SOT223-REG; SOT-223
U2: STM32F042-48; LQFP-48_7x7mm_Pitch0.5mm

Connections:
+5V: C1.1, J1.1, J5.5, J5.7, U1.1
/BOOT: R1.1, SW1.1, U2.44
/D0: J3.1, U2.18, U2.45
/D1: J3.3, U2.19
/D2: J3.5, U2.20, U2.21
/D3: J3.7, U2.22, U2.39
/D4: J4.1, U2.25, U2.40
/D5: J4.3, U2.26, U2.41
/D6: J4.5, U2.27, U2.42
/D7: J4.7, U2.28, U2.43
/SWCLK: J2.2, U2.37
/SWDAT: J2.4, U2.34
/USB_DM: J1.2, U2.32
/USB_DP: J1.3, U2.33
GND: C1.2, C2.2, C3.2, C4.2, C5.2, C6.2, J1.5, J2.3, J3.2, J3.4, J3.6, J3.8, J4.2, J4.4, J4.6, J4.8, J5.2, J5.4, J5.6, J5.8, R1.2, U1.2, U1.4, U2.8, U2.23, U2.35, U2.47
VDD: C2.1, C3.1, C4.1, C5.1, C6.1, J2.1, J5.1, J5.3, SW1.2, U1.3, U2.9, U2.24, U2.36, U2.48

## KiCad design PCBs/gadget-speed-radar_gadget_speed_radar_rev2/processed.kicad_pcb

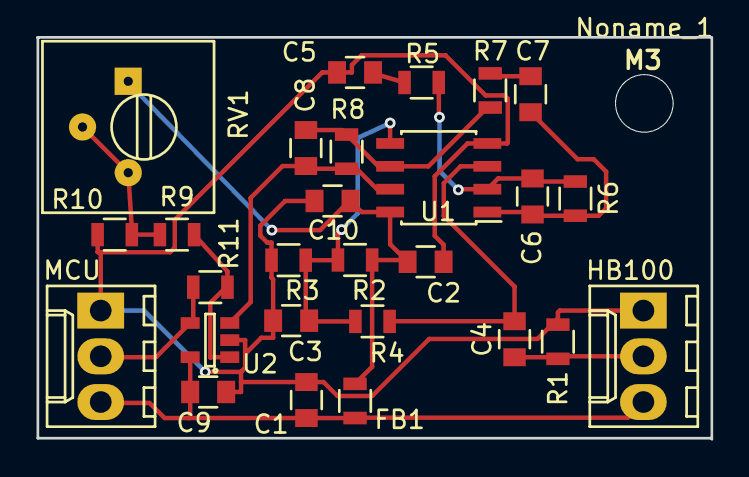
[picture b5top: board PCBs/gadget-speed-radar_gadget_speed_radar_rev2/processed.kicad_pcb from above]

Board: 2 copper layers, 37.5 x 22.3 mm, 28 parts (0 on the bottom side), 15 nets.

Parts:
C1, C2, C3: 10uF; C_0805
C4: 4.7nF; C_0805
C5, C7: 4.7uF; C_0805
C6: 100pF; C_0805
C8: 2.2nF; C_0805
C9, C10: 100nF; C_0805
FB1: FILTER; R_0805
HB100: HB100; Molex_KK-6410-03_03x2.54mm_Straight
MCU: MCU; Molex_KK-6410-03_03x2.54mm_Straight
Noname_1: MountingHole_3.2mm_M3
R1: 12K; R_0805
R2, R3, R5, R10: 10K; R_0805
R4: 330K; R_0805
R6, R8: 1M; R_0805
R7: 8.2K; R_0805
R9: 1K; R_0805
R11: 47K; R_0805
RV1: POT; Potentiometer_Trimmer-Suntan-TSR-3386P
U1: OPA2365; SOIC-8_3.9x4.9mm_Pitch1.27mm
U2: MAX9031; SOT-23-5

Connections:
GND: C1.2, C2.2, C3.2, C5.1, C9.1, C10.2, HB100.1, MCU.3, R1.2, R3.2, R10.2, U1.4, U2.2
unnamed: C3.1, R2.2, R3.1, R4.1, U1.5
unnamed: C4.1, R4.2, U1.3
unnamed: C4.2, HB100.2, R1.1
unnamed: C5.2, R5.1
unnamed: C6.1, C7.2, R6.1, U1.1
unnamed: C6.2, R5.2, R6.2, U1.2
unnamed: C7.1, R7.2
unnamed: C8.1, R8.1, U1.7, U2.3
unnamed: C8.2, R7.1, R8.2, U1.6
unnamed: C2.1, C10.1, FB1.1, R2.1, RV1.1, U1.8
unnamed: MCU.2, R11.1, U2.4
unnamed: R9.1, R10.1, RV1.2, RV1.3
unnamed: R9.2, R11.2, U2.1
VCC: C1.1, C9.2, FB1.2, HB100.3, MCU.1, U2.5

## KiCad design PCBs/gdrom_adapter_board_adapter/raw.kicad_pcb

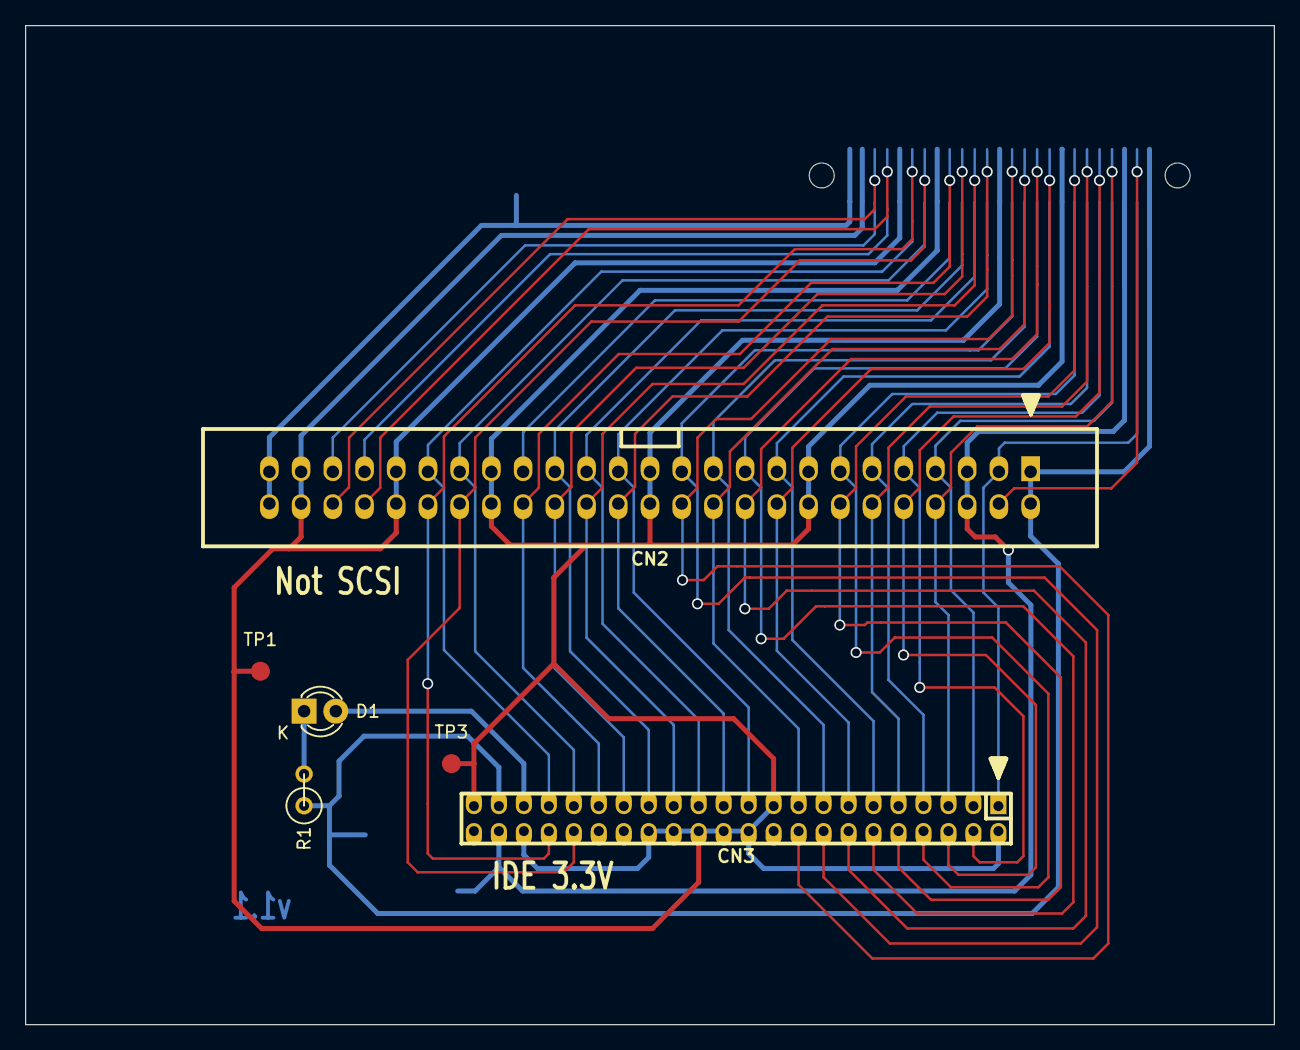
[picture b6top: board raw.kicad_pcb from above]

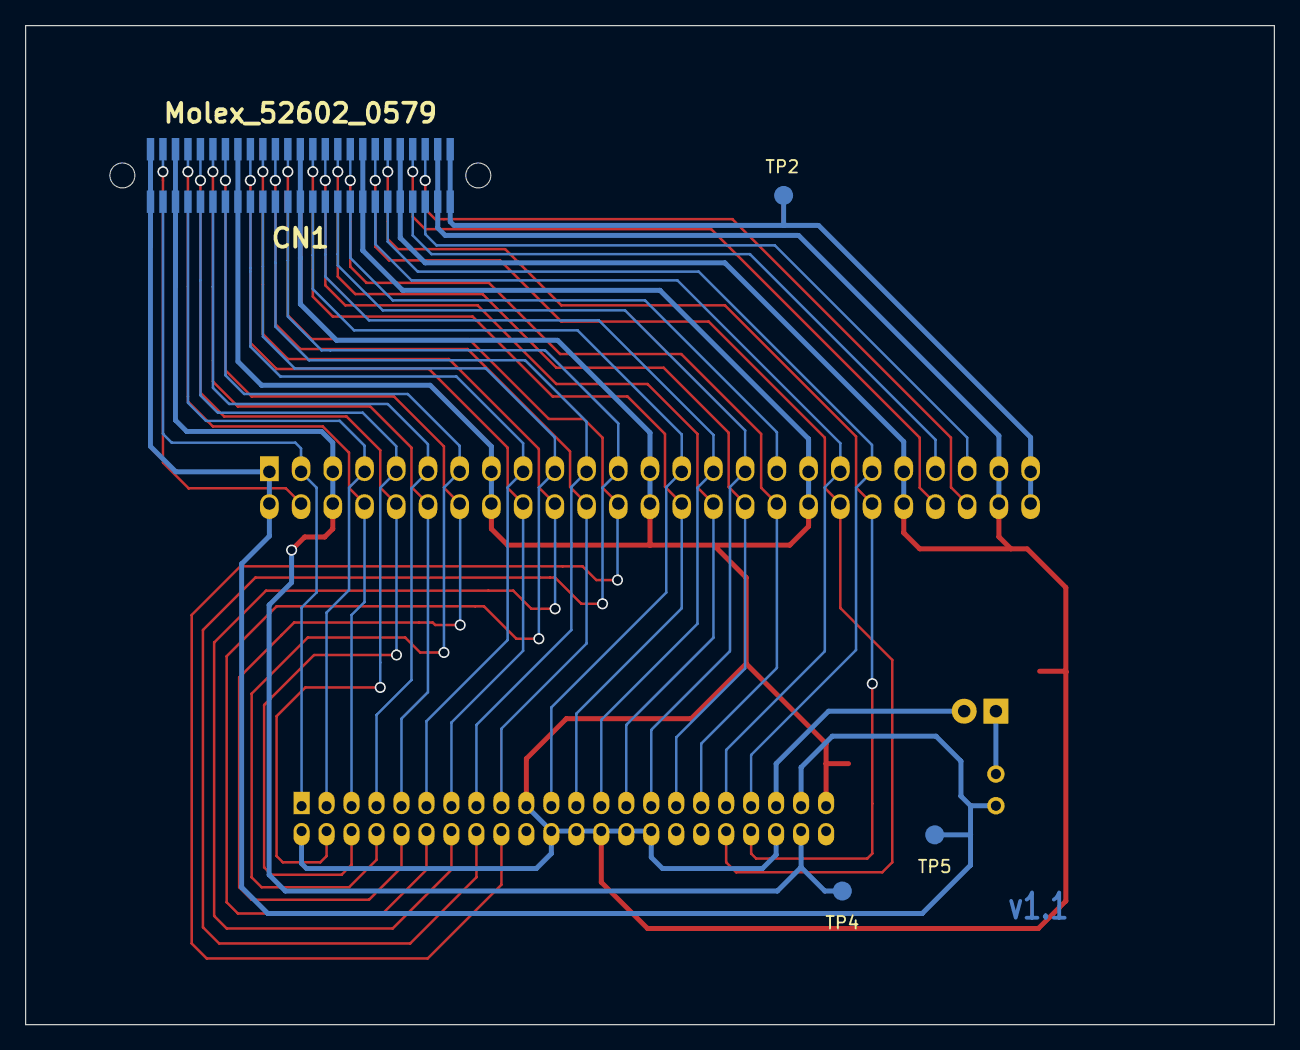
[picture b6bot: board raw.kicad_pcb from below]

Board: 2 copper layers, 100.0 x 80.0 mm, 10 parts (4 on the bottom side), 40 nets.

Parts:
CN1: Molex_52602_0579
CN2: CONN_25X2; vasch_strip_25x2
CN3: CONN_02X22; pin_strip_2mm_22x2
D1: LED; LED-3MM
R1: 1k; R1
TP1, TP2, TP3, TP4, TP5: Measurement_Point_Round-SMD-Pad_Small

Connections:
+3V3: CN1.A1, CN1.B1, CN2.1, CN2.2, CN3.41, R1.1, TP5.1
+5V: CN1.A3, CN1.B3, CN2.5, CN2.6, CN3.42, TP4.1
+12V: CN1.A25, CN1.B25, CN2.49, CN2.50, TP2.1
/A0: CN1.A19, CN2.37, CN3.35
/A1: CN1.B17, CN2.34, CN3.33
/A2: CN1.B19, CN2.38, CN3.36
/ACTIVEn: CN3.39, D1.2
/CD_CLK: CN1.B23, CN2.46
/CS0n: CN1.A20, CN2.39, CN3.37
/CS1n: CN1.B20, CN2.40, CN3.38
/D0: CN1.B11, CN2.22, CN3.17
/D1: CN1.A11, CN2.21, CN3.15
/D2: CN1.B9, CN2.18, CN3.13
/D3: CN1.A9, CN2.17, CN3.11
/D4: CN1.B6, CN2.12, CN3.9
/D5: CN1.A6, CN2.11, CN3.7
/D6: CN1.B4, CN2.8, CN3.5
/D7: CN1.A4, CN2.7, CN3.3
/D8: CN1.A5, CN2.9, CN3.4
/D9: CN1.B5, CN2.10, CN3.6
/D10: CN1.A7, CN2.13, CN3.8
/D11: CN1.B7, CN2.14, CN3.10
/D12: CN1.A10, CN2.19, CN3.12
/D13: CN1.B10, CN2.20, CN3.14
/D14: CN1.A12, CN2.23, CN3.16
/D15: CN1.B12, CN2.24, CN3.18
/DMACKn: CN1.A16, CN2.31, CN3.29
/DMARQ: CN1.A14, CN2.27, CN3.21
/EMPH: CN1.A17, CN2.33
/G_RST: CN1.A2, CN2.3, CN3.1
/INTRQ: CN1.B16, CN2.32, CN3.31
/IORDY: CN1.B15, CN2.30, CN3.27
/LRCK: CN1.B22, CN2.44
/RDn: CN1.A15, CN2.29, CN3.25
/SCK: CN1.A22, CN2.43
/SDAT: CN1.A23, CN2.45
/WRn: CN1.B14, CN2.28, CN3.23
/xB2: CN1.B2, CN2.4
GND: CN1.A8, CN1.A13, CN1.A18, CN1.A21, CN1.A24, CN1.B8, CN1.B13, CN1.B18, CN1.B21, CN1.B24, CN2.15, CN2.16, CN2.25, CN2.26, CN2.35, CN2.36, CN2.41, CN2.42, CN2.47, CN2.48, CN3.2, CN3.19, CN3.22, CN3.24, CN3.26, CN3.28, CN3.30, CN3.40, CN3.43, TP1.1, TP3.1
unnamed: D1.1, R1.2

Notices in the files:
PCBs/front-end-modules_LimeSDR_Sony/processed.kicad_pcb:
Copyright 2016 Lime Microsystems, Ltd.
WORK IS COVERED UNDER A CREATIVE COMMONS LICENSE (CC BY 3.0)
